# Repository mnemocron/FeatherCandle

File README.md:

# Feather Candle "_Guet Nacht - I Love You_"
## 15x7 LED matrix candle based on Adafruit Feather HUZZAH (ESP8266)

---

## Introduction

This electronic project is intended as a romantic gimmik for two long distance lovers.
The candle is connected to the io.adafruit.com cloud over WiFi.

> Whenever one person turns on their own candle, the candle of their lover - on the other side of the world - will light up as well.

The project is built around the Adafruit Feather boards and uses the 15x7 LED matrix and the WiFi enabled Feather HUZZAH board based on the ESP8266 microcontroller. The IoT handling is built around the MQTT service of [io.adafruit.com](https://io.adafruit.com).

### The Name

**_"Guet Nacht"_** is wishing a good night in Swiss German. When I was working on this project I said good night to my loved person by telling them _"Guet Nacht - I love you"_. Ultimately I decided that this is the codename for this project.

---

## Hardware

There are three different variants for the hardware configuration which ultimately determines the functionality and software capabilities. **Yes you can build just the candle without WiFi.**

The candle can also be hung from the ceiling.

### Variant 1: Trinket (just the candle)

This is the most simple and straight forward variant. The essential parts are the [Adafruit 15x7 CharliePlex LED Matrix FeatherWing](https://www.adafruit.com/product/3163) and the [Adafruit Trinket M0](https://www.adafruit.com/product/3500).
This variant is just the candle powered over micro USB.
The micro USB connector is at the top (where the flame is) so the candle could be hanged from the ceiling. Alternatively you can add a [USB Micro-B Breakout Board](https://www.adafruit.com/product/1833) at the bottom of the board to power the candle at the socket.

### Variant 2: Feather (just the candle)

This variant is driven by any Feather board capable of compiling the candle animation sketch. The Feather boards provide an on-board battery charger. At the back of the candle's PCB there is space for a [Keystone 1042P](http://www.keyelco.com/product.cfm/product_id/918) battery holder for a 18650 3.7V battery (this feature is not tested).

### Variant 3: HUZZAH (WiFi enabled)

This is the original Idea. The Trinket holds the code for the flame animation while the Feather HUZZAH is connected to the Adafruit IO cloud. This variant can also be powered by a battery like variant 2. 

##### Battery

This feature remains **untested**. 
Also note that the ESP8266 uses a significant ammount of power, up to 170mA when transmitting data over Wifi ([source](https://bbs.espressif.com/viewtopic.php?t=133)). This may result in very short battery service life).

---

### Building Variant 3

#### Bill of materials (BOM)

This is the partlist for the WiFi enabled candle. 

| Description | Value | Manufacturer | Pcs. | Part. Nr. (mouser) | price (estimation) |
|-------------|------:|--------------|-----:|-------------------:|------------------------:|
| Candle PCB | - | - | 1 |  | $ 10.00 |
| 15x7 CharliePlex LED Matrix FeatherWing (warm white) | - | [Adafruit (3163)](https://www.adafruit.com/product/3163) | 1 | [485-3163](https://www.mouser.com/ProductDetail/Adafruit/3163?qs=%2fha2pyFaduh%252brbpYDT4hI1KcasFFaXTHrw3K2WUgkuI%3d) | $ 13.30 |
| Feather HUZZAH with ESP8266 WiFi | - | [Adafruit (2821)](https://www.adafruit.com/product/2821) | 1 | [485-2821](https://www.mouser.com/ProductDetail/Adafruit/2821?qs=%2fha2pyFadujIGPK6Sj3t4nFuChuwEnz5Imbr6Do1gT8%3d) | $ 18.00 |
| Trinket M0 | - | [Adafruit (3500)](https://www.adafruit.com/product/3500) | 1 | [485-3500](https://www.mouser.com/ProductDetail/Adafruit/3500?qs=%2fha2pyFadugsjdovVS3NFiBTcocohBou1VlJ%2f0Oc5Cc%3d) | $ 9.20 |
| 18650 battery clip SMT | - | [Keystone Electronics](http://www.keyelco.com/product.cfm/product_id/918) | (1) | [534-1042P](https://www.mouser.com/ProductDetail/Keystone-Electronics/1042P?qs=%2fha2pyFadujc2h3Qsi2FB10kgPaLAXTlnLXyd23eJ7VFgPTKWvV%2fxw%3d%3d) | $ 3.10 |
| 18650 Li-Ion battery 3.7V | - | - | (1) |  |  |
| Resistor SMD 1206 | 10k | - | 2 | 
 | $ 0.10 |
| Resistor SMD 1206 | 330R | - | 1 |  | $ 0.10 |
| LED 0805 | - | - | 1 |  |  |
| Pushbutton SMD 12mm | - | - | 1 | eg. [611-PTS125SK43SMTR2](https://www.mouser.com/ProductDetail/611-PTS125SK43SMTR2) | $ 0.50 |
| Pushbutton SMD 6.2mm | - | - | 1 | eg. [611-KSC701GLFS](https://www.mouser.com/ProductDetail/611-KSC701GLFS) | $ 0.50 |
| Capacitor SMD 1206 | 100uF | - | (2) |  |
| Capacitor SMD 0805 | 0.1uF | - | (2) |  |
| USB Micro-B Breakout Board | - |[Adafruit (1833)](https://www.adafruit.com/product/1833) | (1) | [485-1833](https://www.mouser.com/ProductDetail/Adafruit/1833?qs=sGAEpiMZZMsMyYRRhGMFNlzK0q9uz4bUWJaCPx97HuA%3d) | $ 1.50 |
| **Total** * |  |  |  |  | **~$ 50.00** |

> (* The prices are just an estimation. Especially the PCB can only be ordered in larger quantities (>5 pcs).)

> **Important:** The above parts are just for **one** board. In order to build the two connected candles each component is required twice the ammount listed.

> **Notes** 
> - You can either place a 12mm or a 6.2mm push button on the front. (You also need a 6.2mm button on the back).
> - The USB Micro-B Breakout Board is optional for the **variants 1 & 2** (not required on variant 3)
> - **optional**: the capacitors are not required
> - **optional**: the battery holder and the 18650 battery are optional (only work on a **feather variant (2 & 3)**)

#### PCB

You can download the manufacturing files (Gerbers) and use them to order the PCBs from a PCB manufacturer of choice. I recommend using **black solder mask** and **ENIG** surfacing.

Places where you can order custom circuit boards (selection):

> - [OSH Park](https://oshpark.com/)
> - [Aisler](https://aisler.net/products/boards)
> - [DirtyPCBs](http://dirtypcbs.com/store/pcbs)
> - [Elecrow](https://www.elecrow.com/pcb-manufacturing.html)
> - [JLCPCB](https://jlcpcb.com/quote)
> - [PCBCart](https://www.pcbcart.com/)
> - ([Aliexpress](https://www.aliexpress.com/category/521/pcb-pcba.html))

---

## Software

Setting up the Arduino IDE:

> - Download the [Arduitno IDE](https://www.arduino.cc/en/Main/Software)
> - How to up the [Adafruit Trinket M0](https://learn.adafruit.com/adafruit-trinket-m0-circuitpython-arduino/arduino-ide-setup)
> - How to up the [Adafruit Feather HUZZAH](https://learn.adafruit.com/adafruit-feather-huzzah-esp8266/using-arduino-ide)

#### Libraries

The following libraries are required to compile the software in the Arduino IDE.

> - [ESP8266 Arduino](https://github.com/esp8266/Arduino) 
> - [Adafruit IS31FL3731](https://github.com/adafruit/Adafruit_IS31FL3731) 
> - [Adafruit MQTT](https://github.com/adafruit/Adafruit_MQTT_Library) 
> - [Arduino Json](https://github.com/bblanchon/ArduinoJson) 
> - [Wifi Manager](https://github.com/tzapu/WiFiManager) 

### `FeatherCandleTrinket.ino`

This is the Arduino code for the Trinkete M0 which you will need for Variants 1 and 3.

**Note for Variant 1** (just the candle):
You might need to comment the `pinMode(PIN_ONOFF_WEB, INPUT);` on `line 68` so that the input isn't floating and randomly switching the flame on and off.

### `FeatherCandleFeather.ino`

This is the Arduino code soley for Variant 2 where the matrix is powered by any Feather microcontroller board.

### `FeatherCandleHuzzah.ino`

This is the Arduino code you need for the WiFi enabled Variant 3. This goes to the Feather HUZZAH board to connect to the Adafruit IO cloud and control the Trinket M0.

---

## Manual

### Setup the candle (WiFi)

The first time you turn on the candle you will have to configure the WiFi and the MQTT parameters. Luckily the software has a configuration portal built in, so you won't have to hardcode these parameters into the Arduino file.

> This way you can give away a candle to someone who does not know how to program.

### Signing up for Adafruit IO

You need to:
- create an Adafruit account
- log in to [io.adafruit.com](https://io.adafruit.com)
- create a new feed called `candle`

You need the following values to continue:
- `username` (find it on [accounts.adafruit.com](https://accounts.adafruit.com/))
- `key` (find it on [io.adafruit.com](https://learn.adafruit.com/mqtt-adafruit-io-and-you/getting-started-on-adafruit-io#where-to-find-your-adafruit-dot-io-key))
- `feed` (the feed your just created: `candle`)

You can find more detailed instructions on how to get started with Adafruit IO on Adafruit's learning platform: [learn.adafruit.com](https://learn.adafruit.com/mqtt-adafruit-io-and-you/getting-started-on-adafruit-io)

**If you give away one candle to your lover:**

> **Important** Both candles require the same values for `username` / `key` / `feed` in order to be synchronized.

Your partner does not require an Adafruit account. Just give them your own `username` / `key` / `feed` so that they can set up their candle as follows:

#### To start the candle in configuration mode:

Hold the button on the back of the candle and turn on the feather candle. You can do this two ways:
- hold the button on the back then plug in the USB connector to power the device on
- hold the button on the back then press the reset button on the Feather HUZZAH itself while power is already on

finally release the button on the back.

Take your phone or computer and search for WiFi networks. You should see a network called `Feather Candle` - the password is `iloveyou`.

If you have successfully connected to the access point it should direct you to a "sign-in" page. If this does not happen just open your browser and open the webpage [10.0.1.1](http://10.0.1.1). On this page you have 4 buttons available.

##### `Info`

This page shows you the MAC address and other information about the ESP8266 that is on the Feather HUZZAH.

##### `Configure WiFi`

In the most cases this is the only page that you will need.

Choose a WiFi network on the list of available networks and enter the password.

**The ESP8266 only works with 2.4GHz networks.**

On this page you have a bunch of other values that you can configure.

| Name | Description | Default | need to change? |
|------|-------------|--------:|-----------------|
| `mqtt_server` | address to the MQTT server | `io.adafrtuit.com` | no |
| `mqtt_port` | MQTT server port | `1883` | no |
| `aio_key` | Adafruit IO key |  | yes |
| `aio_username` | Adafruit IO username |  | yes |
| `aio_feed` | Adafruit IO feed | `candle` | optional (*) |
| `aio_poll_interval` | interval to check for changes in [s] | `3` | optional (**) |
| `aio_last_will` | last value to send on disconnect | `0` | optional |

(*) the name of your Adafruit IO feed

(**) not implemented yet, see issues - default value is 3 seconds

---

## Inspiration

### mori.london

>mori.london sets out to define a completely new category of LED lighting: playful, emotional, atmospheric and elegant, always innovative and always low power and low impact on the environment.

[www.mori.london](https://www.mori.london/)

Developer: [Jaco Burge](http://jacoburge.co.uk/morilondon-candles/)

### My New Flame

by Moritz Waldemeyer & Ingo Maurer

[www.ingo-maurer.com](https://www.ingo-maurer.com/en/products/my-new-flame)

### Adafruit Animated Flame Pendant

> Turn on your heartlight.
Let it shine wherever you go.
Let it make a happy glow.
For all the world to see.

[learn.adafruit.com](https://learn.adafruit.com/animated-flame-pendant/overview)

---

#### Issues

- `[wontfix]` one of the through hole clips on the battery holder must be cut off in order to mount it on the backside of the PCB

#### ToDo

☐ test battery lifetime

☐ add secure api interface (https requests / port 8883 for SSL)

---

## Credits

- [wbphelps](https://github.com/wbphelps/FeatherCandle) - FeatherCandle Software for 15x7 Feather Wing LED matrix
- [Adafruit](https://learn.adafruit.com/animated-flame-pendant/overview) - Tutorial and software for the Flame Pendant
- [tzapu](https://github.com/tzapu/WiFiManager) - WiFiManager library and example code
- [bblanchon](https://github.com/bblanchon/ArduinoJson) - Arduino Json library

---

> Adafruit invests time and resources providing this open source design, please support Adafruit and open-source hardware by purchasing products from Adafruit!

---

## License

Creative Commons Attribution-ShareAlike 4.0 [CC BY-SA 4.0](https://creativecommons.org/licenses/by-sa/4.0/)

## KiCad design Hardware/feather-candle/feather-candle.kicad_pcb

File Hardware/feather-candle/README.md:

# Feather Candle "_Guet Nacht - I Love You_"
## 15x7 LED matrix candle based on Adafruit Feather HUZZAH (ESP8266)

---

## Hardware

KiCAD project and gerber files.

__Note__

`feather-candle-gerbers-2018-02-23.zip` are the previous gerbers which contain some issues.

---

## License

Creative Commons Attribution-ShareAlike 4.0 [CC BY-SA 4.0](https://creativecommons.org/licenses/by-sa/4.0/)

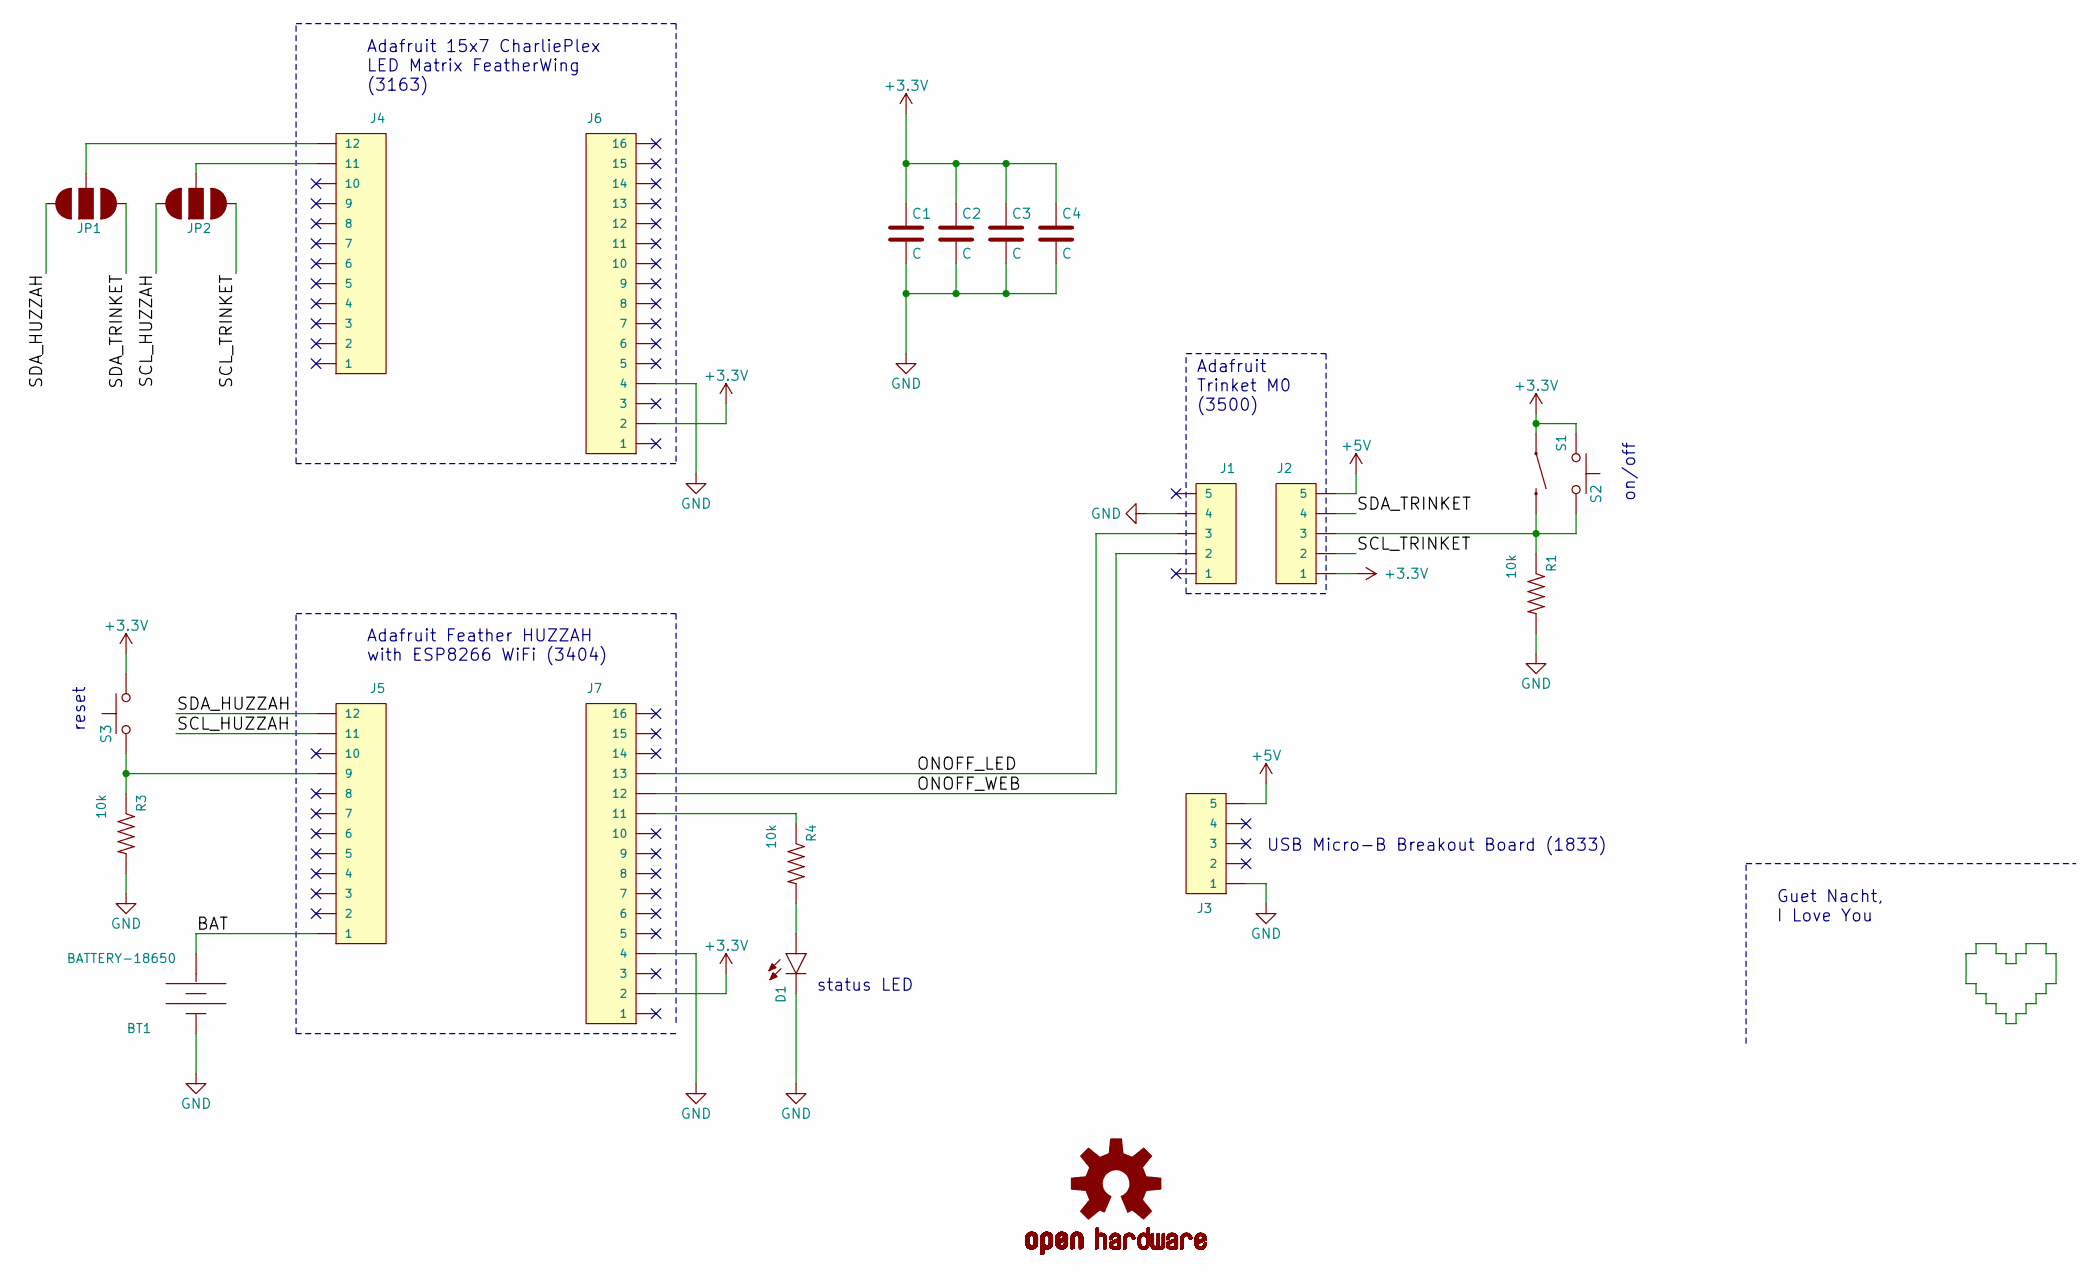
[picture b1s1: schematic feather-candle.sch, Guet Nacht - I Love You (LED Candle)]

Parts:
BT1: BATTERY-18650; BATTERY_18650-HOLDER_1042P
C1, C2: C; C_0805_HandSoldering
C3, C4: C; C_1210_HandSoldering
D1: LED-RED0603; LED-0603
J1, J2, J3: CONN_05; 1X05_NO_SILK
J4, J5: CONN_121X12_NO_SILK_KIT; 1X12_NO_SILK_KIT
J6, J7: CONN_161X16_NO_SILK; 1X16_NO_SILK
JP1, JP2: JUMPER-SMT_3_NO; SMT-JUMPER_3_NO_NO-SILK
LOGO1: OSHW-LOGOM; OSHW-Logo_12mm_copper
R1, R3, R4: 10k; 1206
S1: MOMENTARY-SWITCH-SPST-PTH-6.0MM; TACTILE_SWITCH_SMD_12MM
S2, S3: SW_Push; TACTILE_SWITCH_SMD_6.2MM_TALL

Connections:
+3V3: C1.1, C2.1, C3.1, C4.1, J2.1, J6.2, J7.2, S1.1, S2.1, S3.1
+5V: J2.5, J3.5
/BAT: BT1.PWR@ (+), J5.1
/ONOFF_LED: J1.3, J7.13
/ONOFF_WEB: J1.2, J7.12
/SCL_HUZZAH: J5.11, JP2.3
/SCL_TRINKET: J2.2, JP2.1
/SDA_HUZZAH: J5.12, JP1.3
/SDA_TRINKET: J2.4, JP1.1
GND: BT1.GND@ (-), C1.2, C2.2, C3.2, C4.2, D1.C, J1.4, J3.1, J6.4, J7.4, R1.2, R3.2
unnamed: D1.A, R4.2
unnamed: J2.3, R1.1, S1.3 (2), S2.2
unnamed: J4.11, JP2.2
unnamed: J4.12, JP1.2
unnamed: J5.9, R3.1, S3.2
unnamed: J7.11, R4.1

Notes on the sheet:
Guet Nacht, I Love You
Adafruit Feather HUZZAH with ESP8266 WiFi (3404)
status LED
USB Micro-B Breakout Board (1833)
on/off
Adafruit Trinket M0 (3500)
reset
Adafruit 15x7 CharliePlex LED Matrix FeatherWing (3163)

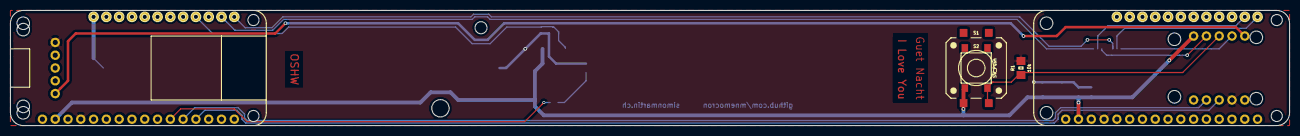
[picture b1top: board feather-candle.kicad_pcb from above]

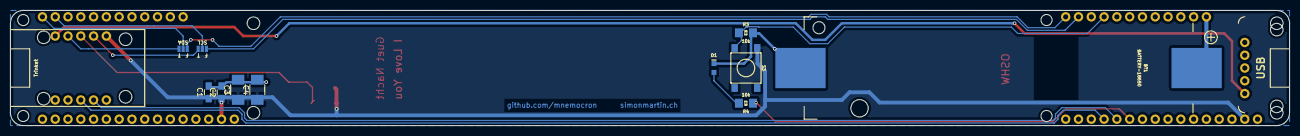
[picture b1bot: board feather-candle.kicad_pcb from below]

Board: 2 copper layers, 254.0 x 22.9 mm, 22 parts (14 on the bottom side), 16 nets.

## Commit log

2018-03-13 initial commit (wip)
2018-03-13 deleted sub-repository
2018-03-13 added candle firmware for Trinket M0
2018-03-23 initial commit of the firmware
2018-03-25 Fixed several issues with the PCB layout. Correct hole placement of the 1042 battery holder. Correct mounting hole placement of the Feather boards. Changed resistor footprints to 1206 and 0805_HandSo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
2018-03-30 first release
2018-04-06 removed wip.md
2018-05-24 typo errors ;-)
